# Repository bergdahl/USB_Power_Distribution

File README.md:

# USB_Power_Distribution

Autodesk Eagle files for a simple USB power distribution board. 
Also included is Fusion 360 file containing a simple enclosure for 3D printing.

# License 

Copyright (c) 2020, Bergdahl IT AB. All rights reserved.

This library is open source. It is released under the [MIT License](LICENSE.txt). Please see the included LICENSE.txt file for more information.

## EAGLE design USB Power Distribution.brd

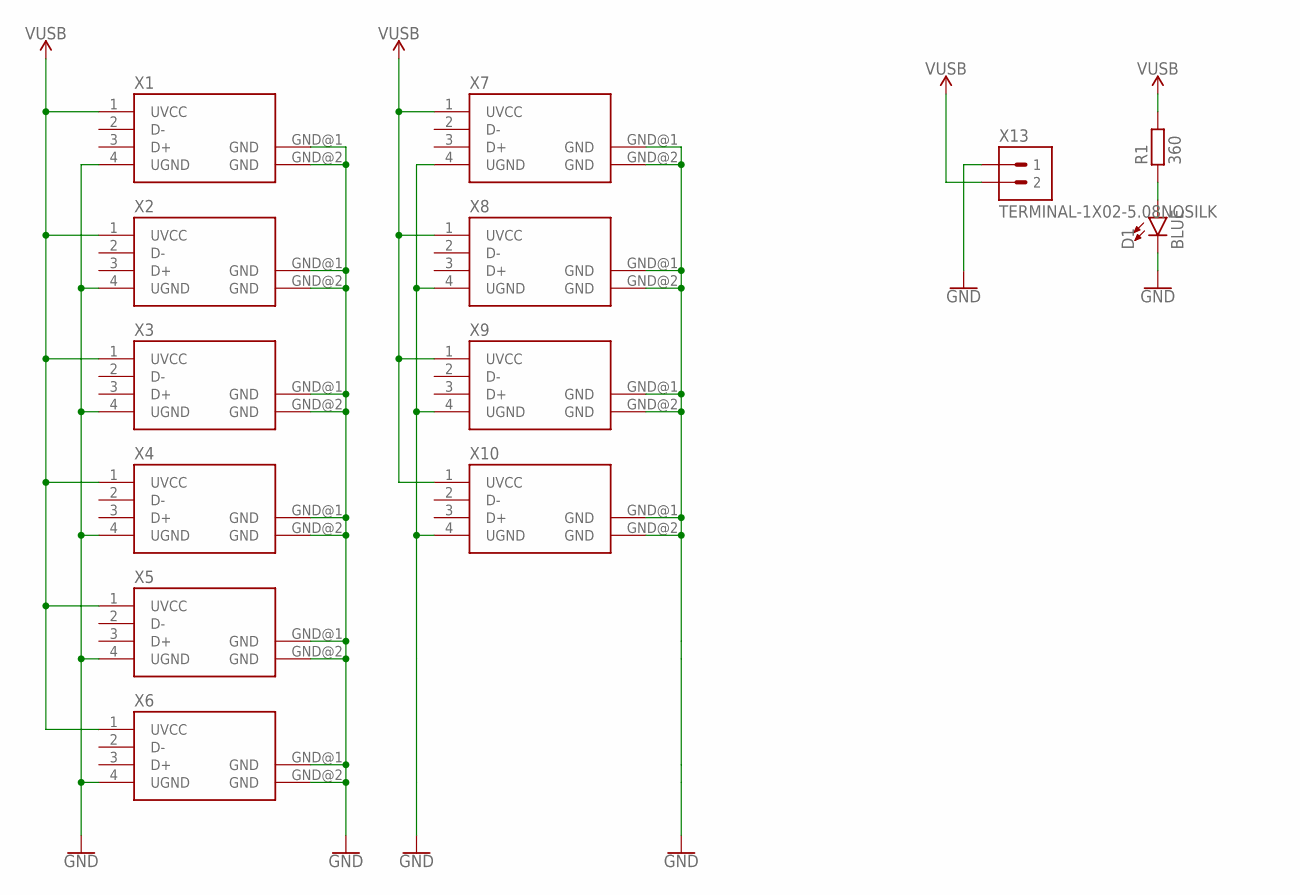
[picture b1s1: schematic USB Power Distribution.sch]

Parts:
D1: BLUE; LED3MM
R1: 360; R0805
X1, X2, X3, X4, X5, X6, X7, X8, X9, X10: USB-AVERT-SS-52100-002; USB-A-VERT-SS-52100-002
X13: TERMINAL-1X02-5.08NOSILK; TERMINAL-5.08-2P-NO-SILK

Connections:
GND: D1.K (C), X1.4 (UGND), X1.GND@1 (GND), X1.GND@2 (GND), X2.4 (UGND), X2.GND@1 (GND), X2.GND@2 (GND), X3.4 (UGND), X3.GND@1 (GND), X3.GND@2 (GND), X4.4 (UGND), X4.GND@1 (GND), X4.GND@2 (GND), X5.4 (UGND), X5.GND@1 (GND), X5.GND@2 (GND), X6.4 (UGND), X6.GND@1 (GND), X6.GND@2 (GND), X7.4 (UGND), X7.GND@1 (GND), X7.GND@2 (GND), X8.4 (UGND), X8.GND@1 (GND), X8.GND@2 (GND), X9.4 (UGND), X9.GND@1 (GND), X9.GND@2 (GND), X10.4 (UGND), X10.GND@1 (GND), X10.GND@2 (GND), X13.P$1 (1)
unnamed: D1.A, R1.1
VUSB: R1.2, X1.1 (UVCC), X2.1 (UVCC), X3.1 (UVCC), X4.1 (UVCC), X5.1 (UVCC), X6.1 (UVCC), X7.1 (UVCC), X8.1 (UVCC), X9.1 (UVCC), X10.1 (UVCC), X13.P$2 (2)

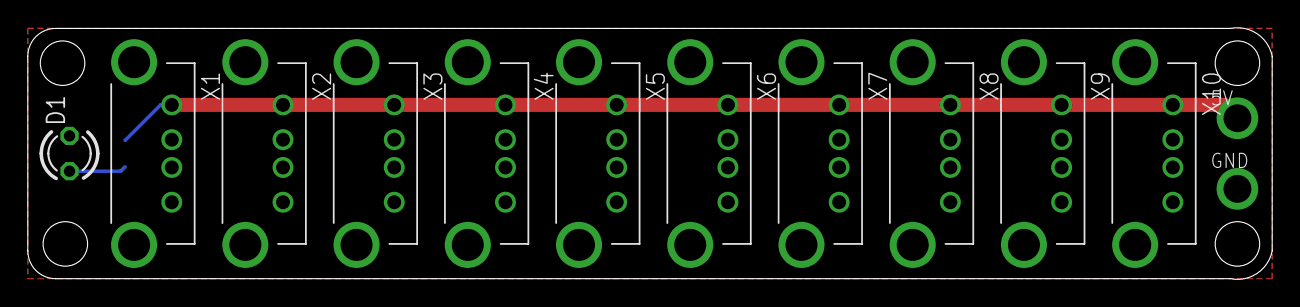
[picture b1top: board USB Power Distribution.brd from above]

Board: 2 copper layers, 89.5 x 18.1 mm, 13 parts (1 on the bottom side), 3 nets.

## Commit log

2020-04-19 Fixed spelling
